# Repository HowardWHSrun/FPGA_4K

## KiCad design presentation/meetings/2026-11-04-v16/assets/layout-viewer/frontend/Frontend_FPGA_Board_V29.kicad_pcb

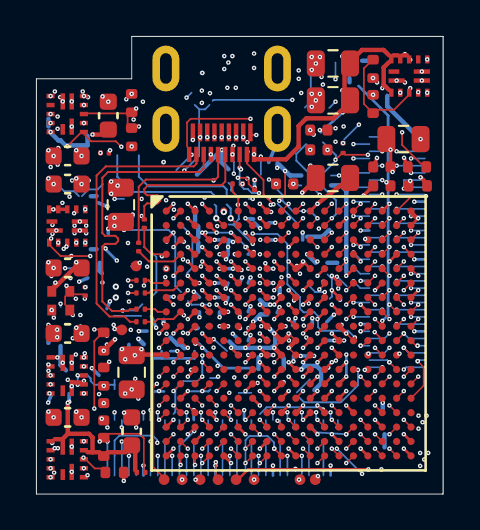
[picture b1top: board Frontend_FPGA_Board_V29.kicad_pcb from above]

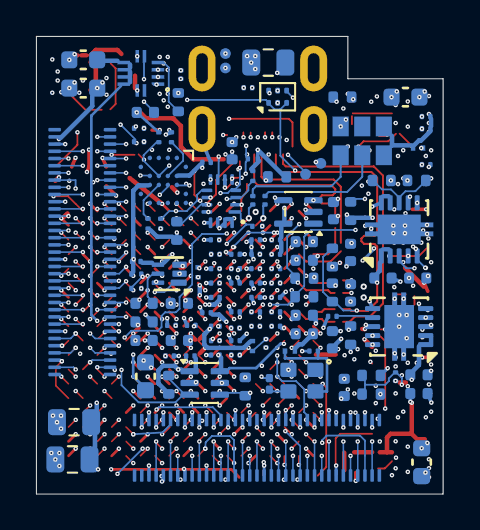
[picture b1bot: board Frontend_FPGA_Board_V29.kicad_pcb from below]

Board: 10 copper layers, 22.6 x 25.4 mm, 184 parts (124 on the bottom side), 191 nets.

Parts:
C1, C2, C12, C13, C21, C22, C85, C86: 22uF; C_0603_1608Metric
C3, C14, C23, C87: 22pF; C_0201_GRM03_Murata_0p22Gap
C4, C10, C89: 100uF; C_0805_2012Metric
C5, C6, C16, C17, C24, C25, C30, C31, C36, C37, C43, C44, C45, C47, C48, C49, C51, C54, C90, C94, C95, C96, C101: 4.7uF; C_0402_1005Metric
C7, C8, C9, C11, C18, C19, C20, C26, C27, C28, C29, C32, C33, C34, C35, C38, C39, C40, C52, C53, C55, C56, C57, C58, C80, C91, C92, C93, C97, C98, C99, C100: 470nF; C_0201_GRM03_Murata_0p22Gap
C15, C42, C59: 47uF; C_0805_2012Metric
C46, C50: 10nF; C_0201_GRM03_Murata_0p22Gap
C60, C63, C78, C79, C81, C82, C83, C88, C105, C106, C200, C201, C202, C203, C204, C205: 100nF; C_0201_GRM03_Murata_0p22Gap
C61, C84: 1uF; C_0402_1005Metric
C62: 220nF; C_0201_GRM03_Murata_0p22Gap
C75, C76, C102, C104: 22uF / 6.3V; C_0603_1608Metric
C77: 22nF / 50V; C_0402_1005Metric
C103: 470nF / 6.3V; C_0201_GRM03_Murata_0p22Gap
C206, C207, C208: 22uF / 10V; C_0805_2012Metric
J1, J2: DF40C-70DS-0.4V(51); Hirose_DF40C-70DS-0.4V_2x35_P0.4mm
J3: Micro-HDMI 467651001; Molex_MicroHDMI_46765_1xxx
L1, L2, L3, L4: MPZ0603S121HT000; TDK_MPZ0603S121HT000_0201_Land_0p25x0p30_Gap0p30
R1, R4, R5, R41, R55, R59: 200k; R_0402_1005Metric
R2: 301k; R_0402_1005Metric
R3, R9, R11, R12, R14, R17, R18, R19, R22, R38, R43, R58: 4.99k; R_0402_1005Metric
R7: 150k; R_0402_TE_CPF_Reflow_0p50Gap
R8: 100k; R_0402_TE_CPF_Reflow_0p50Gap
R10: 1.3k; R_0402_1005Metric
R13: 2.49k; R_0402_1005Metric
R16: 100R; R_0201_ERA1A_Panasonic_0p30Gap
R20, R21, R49, R50: 4.7k; R_0201_ERA1A_Panasonic_0p30Gap
R25: 470R; R_0402_1005Metric
R27: 1k; R_0201_ERA1A_Panasonic_0p30Gap
R37: 24k / 1%; R_0402_1005Metric
R42: 150k; R_0402_1005Metric
R44: 33R; R_0201_0603Metric
R45: 4.64k; R_0201_ERA1A_Panasonic_0p30Gap
R46, R47, R48: 10k; R_0201_ERA1A_Panasonic_0p30Gap
R51, R52, R53: 47k; R_0201_ERA1A_Panasonic_0p30Gap
R54: 22k; R_0201_ERA1A_Panasonic_0p30Gap
R57: 10k; R_0402_1005Metric
R60: 44.2k; R_0402_1005Metric
TP1, TP2, TP3, TP4, TP5, TP6, TP7, TP8, TP9, TP10, TP11, TP12, TP13, TP14: 0.6mm COPPER; TestPoint_Pad_D0.6mm_Edge_NoPaste
U1: XC7A35T-2CSG325I; Xilinx_CSG325
U2, U3, U4, U13, U16: MPM3834CGPA; MPM3834C_ECLGA14_2.5x2.5mm
U5, U6: TPS74801DRCRM3; VSON-10-1EP_3x3mm_P0.5mm_EP1.65x2.4mm
U7: W25Q128JWYIQ; Winbond_WLCSP-21_P0.5mm
U8: SN74AVC4T774RSVR / SPI x1; TI_RSV_UQFN16_1.8x2.6mm_P0.4mm
U10: MP5077GG-Z; MPS_MP5077_QFN12_2x2mm_P0.4mm
U11: 74AUP2G07GM / dual reset OD; Nexperia_SOT886_XSON6_1x1.45mm
U12: TPS389001 / timed rail-ready reset; TI_DSE0006A_WSON6_1p5x1p5_P0p5_Manufacturer
U14: SN74AUP1G14 / SPI OE; TI_DCK_SC70_5
U15: SN74AXC1T45DCKR; SOT-363_SC-70-6
Y1: AX3DAF1-125.0000T3 / 125 MHz; Abracon_AX3_3225_6pin
Y2: SiT1615A / 25 MHz / 1.5 V; SiTime_2016_4pin

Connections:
1V4_GTP_IN: C43.2, C47.2, C86.1, C87.1, R41.1, U5.1 (IN), U5.2 (IN), U6.1 (IN), U6.2 (IN), U13.6 (OUT_S), U13.9 (OUT), U13.10 (OUT)
/ASIC1_CLK32MHz_Out: J1.11, U1.P15 (L11P_T1_SRCC)
/ASIC1_DATA1: J1.3, U1.M16 (L7P_T1_D09)
/ASIC1_DATA2: J1.4, U1.N18 (L10P_T1_D14)
/ASIC1_DATA3: J1.5, U1.M17 (L7N_T1_D10)
/ASIC1_DATA4: J1.6, U1.P18 (L10N_T1_D15)
/ASIC1_DATA5: J1.7, U1.N16 (L9P_T1_DQS)
/ASIC1_DATA6: J1.8, U1.L18 (L4N_T0_D05)
/ASIC1_DATA7: J1.9, U1.K15 (L5N_T0_D07)
/ASIC1_DATA8: J1.10, U1.K18 (L3N_T0_DQS_EMCCLK)
/ASIC1_READ: J1.12, U1.K17 (L4P_T0_D04)
/ASIC1_SYNC: J1.13, U1.J15 (L2P_T0_D02)
/ASIC2_CLK32MHz_Out: J1.23, U1.E16 (L14P_T2_SRCC)
/ASIC2_DATA1: J1.18, U1.H18 (L23N_T3_FWE_B)
/ASIC2_DATA2: J1.21, U1.G14 (L22P_T3_A17)
/ASIC2_DATA3: J1.16, U1.H16 (L20P_T3_A20)
/ASIC2_DATA4: J1.17, U1.H14 (IO25)
/ASIC2_DATA5: J1.20, U1.H17 (L23P_T3_FOE_B)
/ASIC2_DATA6: J1.24, U1.G16 (L20N_T3_A19)
/ASIC2_DATA7: J1.22, U1.G17 (L19P_T3_A22)
/ASIC2_DATA8: J1.19, U1.G15 (L21P_T3_DQS)
/ASIC2_READ: J1.25, U1.F14 (L22N_T3_A16)
/ASIC2_SYNC: J1.26, U1.F18 (L19N_T3_A21_VREF)
/ASIC3_CLK32MHz_Out: J1.36, U1.E15 (L13P_T2_MRCC)
/ASIC3_DATA1: J1.31, U1.F15 (L21N_T3_DQS_A18)
/ASIC3_DATA2: J1.28, U1.F17 (L24P_T3_RS1)
/ASIC3_DATA3: J1.35, U1.D14 (L12N_T1_MRCC)
/ASIC3_DATA4: J1.30, U1.E18 (L24N_T3_RS0)
/ASIC3_DATA5: J1.29, U1.E13 (L12P_T1_MRCC)
/ASIC3_DATA6: J1.32, U1.E17 (L17P_T2_A26)
/ASIC3_DATA7: J1.39, U1.D15 (L13N_T2_MRCC)
/ASIC3_DATA8: J1.33, U1.D11 (L6P_T0)
/ASIC3_READ: J1.37, U1.C11 (L4P_T0)
/ASIC3_SYNC: J1.38, U1.D18 (L17N_T2_A25)
/ASIC4_CLK32MHz_Out: J1.43, U1.D13 (L11P_T1_SRCC)
/ASIC4_DATA1: J1.44, U1.C14 (L9P_T1_DQS_AD3P)
/ASIC4_DATA2: J1.40, U1.D16 (L14N_T2_SRCC)
/ASIC4_DATA3: J1.47, U1.C13 (L11N_T1_SRCC)
/ASIC4_DATA4: J1.45, U1.C9 (L2N_T0_AD8N)
/ASIC4_DATA5: J1.49, U1.C12 (L6N_T0_VREF)
/ASIC4_DATA6: J1.42, U1.C16 (L16P_T2_A28)
/ASIC4_DATA7: J1.53, U1.B12 (L7P_T1_AD2P)
/ASIC4_DATA8: J1.46, U1.B16 (L15P_T2_DQS)
/ASIC4_READ: J1.48, U1.B15 (L9N_T1_DQS_AD3N)
/ASIC4_SYNC: J1.51, U1.A13 (L8P_T1_AD10P)
/ASIC5_CLK32MHz_Out: J2.7, U1.R2 (L13P_T2_MRCC)
/ASIC5_DATA1: J2.11, U1.N2 (L11N_T1_SRCC)
/ASIC5_DATA2: J2.6, U1.U1 (L15N_T2_DQS)
/ASIC5_DATA3: J2.4, U1.P1 (L9N_T1_DQS)
/ASIC5_DATA4: J2.3, U1.N1 (L9P_T1_DQS)
/ASIC5_DATA5: J2.5, U1.K1 (L3N_T0_DQS)
/ASIC5_DATA6: J2.12, U1.U6 (L20P_T3)
/ASIC5_DATA7: J2.13, U1.L2 (L4N_T0)
/ASIC5_DATA8: J2.10, U1.U2 (L15P_T2_DQS)
/ASIC5_READ: J2.8, U1.T2 (L14N_T2_SRCC)
/ASIC5_SYNC: J2.9, U1.M1 (L7N_T1)
/ASIC6_CLK32MHz_Out: J2.20, U1.R3 (L14P_T2_SRCC)
/ASIC6_DATA1: J2.16, U1.R1 (L13N_T2_MRCC)
/ASIC6_DATA2: J2.19, U1.M2 (L7P_T1)
/ASIC6_DATA3: J2.24, U1.T4 (L17P_T2)
/ASIC6_DATA4: J2.17, U1.K2 (L3P_T0_DQS)
/ASIC6_DATA5: J2.18, U1.T3 (L17N_T2)
/ASIC6_DATA6: J2.25, U1.L3 (L5N_T0)
/ASIC6_DATA7: J2.22, U1.U4 (L18P_T2)
/ASIC6_DATA8: J2.23, U1.P3 (L12N_T1_MRCC)
/ASIC6_READ: J2.21, U1.K3 (L4P_T0)
/ASIC6_SYNC: J2.26, U1.V6 (L23N_T3)
/ASIC7_CLK32MHz_Out: J2.31, U1.P4 (L12P_T1_MRCC)
/ASIC7_DATA1: J2.33, U1.N4 (L10N_T1)
/ASIC7_DATA2: J2.30, U1.V4 (L18N_T2)
/ASIC7_DATA3: J2.29, U1.M4 (L10P_T1)
/ASIC7_DATA4: J2.36, U1.U7 (L23P_T3)
/ASIC7_DATA5: J2.28, U1.T5 (L21N_T3_DQS)
/ASIC7_DATA6: J2.32, U1.U5 (L20N_T3)
/ASIC7_DATA7: J2.35, U1.R5 (L21P_T3_DQS)
/ASIC7_DATA8: J2.37, U1.R6 (IO25)
/ASIC7_READ: J2.39, U1.R7 (L22P_T3)
/ASIC7_SYNC: J2.38, U1.V7 (L24N_T3)
/ASIC8_CLK32MHz_Out: J2.49, U1.R16 (L14P_T2_SRCC)
/ASIC8_DATA1: J2.53, U1.R17 (L14N_T2_SRCC)
/ASIC8_DATA2: J2.46, U1.V12 (L21P_T3_DQS)
/ASIC8_DATA3: J2.40, U1.U9 (L24P_T3_A01_D17)
/ASIC8_DATA4: J2.48, U1.U12 (L22N_T3_A04_D20)
/ASIC8_DATA5: J2.47, U1.T13 (L19N_T3_A09_D25_VREF)
/ASIC8_DATA6: J2.43, U1.U11 (L23P_T3_A03_D19)
/ASIC8_DATA7: J2.45, U1.T12 (L22P_T3_A05_D21)
/ASIC8_DATA8: J2.44, U1.V11 (L23N_T3_A02_D18)
/ASIC8_READ: J2.42, U1.V9 (L24N_T3_A00_D16)
/ASIC8_SYNC: J2.51, U1.T17 (L16P_T2_CSI_B)
/CLK25_RAW: R44.1, Y2.3 (OUT)
/CLK25_VDD: C88.1, L3.2, Y2.4 (VDD)
/FB_GTP_1V4: C87.2, R41.2, R42.1, U13.5 (FB)
/FB_VIN_3V3: R59.2, R60.1, U16.5 (FB)
/FE_RESET_SHARED: J1.64, U1.A15 (L10N_T1_AD11N)
/GPIO_CMD_N: J3.14 (GPIO_CMD_N), U1.V2 (L16N_T2)
/GPIO_CMD_P: J3.12 (GPIO_CMD_P), U1.V3 (L16P_T2)
/IMP_TST_SHARED: J1.63, U1.A12 (L7N_T1_AD2N)
/NONSTIM_BOARD1_SPI_DL: J1.58, U1.B17 (L16N_T2_A27)
/NONSTIM_BOARD1_SPI_DR: J1.59, U1.B11 (L4N_T0)
/NONSTIM_BOARD2_SPI_DL: J2.63, U1.U16 (L17N_T2_A13_D29)
/NONSTIM_BOARD2_SPI_DR: J2.59, U1.T14 (L13P_T2_MRCC)
/STIM_CHIP1_SPI_DL: J1.65, U1.A9 (L3N_T0_DQS_AD1N)
/STIM_CHIP1_SPI_DR: J1.60, U1.B14 (L10P_T1_AD11P)
/STIM_CHIP2_SPI_DL: J1.62, U1.A17 (L15N_T2_DQS_ADV_B)
/STIM_CHIP3_SPI_DL: J2.56, U1.V13 (L21N_T3_DQS_A06_D22)
/STIM_CHIP4_SPI_DR: J2.61, U1.T15 (L13N_T2_MRCC)
BOARD1_CLK: J1.56, U1.C17 (L18P_T2_A24)
BOARD1_SPI_CLK: J1.54, U1.C18 (L18N_T2_A23)
BOARD2_CLK: J1.61, U1.A10 (L5N_T0_AD9N)
BOARD2_SPI_CLK: J1.55, U1.B10 (L5P_T0_AD9P)
BOARD3_CLK: J2.54, U1.V8 (L24P_T3)
BOARD3_SPI_CLK: J2.55, U1.U10 (IO25)
BOARD4_CLK: J2.52, U1.T7 (L22N_T3)
BOARD4_SPI_CLK: J2.65, U1.T18 (L15N_T2_DQS_DOUT_CSO_B)
BOOT_RAILS_PG_3V3: R9.2, TP10.1 (PAD_1), U4.11 (PG), U5.3 (PG), U12.3 (MR_PG)
BOOT_RESET_N: R47.2, U11.1 (1A_RESET_N), U11.3 (2A_RESET_N), U12.6 (RESET_N_OD), U14.2 (A_RESET_N)
CABLE_TARGET_SENSE: J3.1 (SENSE), R27.2
CHIP_RESET_SHARED: J1.52, U1.J16 (L2N_T0_D03)
CLK25_PL: R44.2, U1.N3 (L11P_T1_SRCC)
EN_GTPWR_1V5: R58.2, U1.M15 (L6N_T0_D08_VREF), U15.3 (A)
EN_GTPWR_3V3: R57.1, U13.3 (EN), U15.4 (B)
FLASH_CS_N_1V8: R22.2, U7.1, U8.11 (B2_CS)
FLASH_DQ0_1V8: R53.2, U7.5, U8.10 (B3_MOSI)
FLASH_DQ1_1V8: R51.1, U7.2, U8.9 (B4_MISO)
FLASH_HOLD_N_1V8: R21.2, U7.7
FLASH_READY_SENSE: R45.2, R46.1, U12.1 (SENSE_DIV)
FLASH_SCK_1V8: R52.1, U7.6, U8.12 (B1_SCK)
FLASH_TRANSLATOR_OE_N: R48.2, U8.7 (OE_N), U14.4 (Y_OE_N)
FLASH_WP_N_1V8: R20.2, U7.3
FPGA_DONE: R38.2, TP12.1 (PAD_1), U1.F12 (DONE_0)
FPGA_INIT_B: R18.2, TP11.1 (PAD_1), U1.T10 (INIT_B_0), U11.4 (2Y_INIT_OD)
FPGA_JTAG_TCK: J3.17 (TCK), U1.F8 (TCK_0)
FPGA_JTAG_TDI: J3.15 (TDI), U1.T9 (TDI_0)
FPGA_JTAG_TDO: J3.18 (TDO), U1.T8 (TDO_0)
FPGA_JTAG_TMS: J3.2 (TMS), U1.R8 (TMS_0)
FPGA_PROGRAM_B: R17.2, U1.P10 (PROGRAM_B_0), U11.6 (1Y_PROGRAM_OD)
FPGA_PUDC_B: R25.2, U1.J18 (L3P_T0_DQS_PUDC_B)
FPGA_QSPI_CCLK: R49.2, U1.E8 (CCLK_0), U8.1 (A1_CCLK)
FPGA_QSPI_CS_N: R19.2, U1.L15 (L6P_T0_FCS_B), U8.2 (A2_CS)
FPGA_QSPI_DQ0: R50.2, U1.K16 (L1P_T0_D00_MOSI), U8.3 (A3_MOSI)
FPGA_QSPI_DQ1: R54.1, U1.L17 (L1N_T0_D01_DIN), U8.4 (A4_MISO)
GND: C1.2, C2.2, C4.2, C5.2, C6.2, C7.2, C8.2, C9.2, C10.2, C11.2, C12.2, C13.2, C15.2, C16.2, C17.2, C18.2, C19.2, C20.2, C21.2, C22.2, C24.2, C25.2, C26.2, C27.2, C28.2, C29.2, C30.2, C31.2, C32.2, C33.2, C34.2, C35.2, C36.2, C37.2, C38.2, C39.2, C40.2, C42.2, C43.1, C44.2, C45.2, C46.2, C47.1, C48.2, C49.2, C50.2, C51.2, C52.2, C53.2, C54.2, C55.2, C56.2, C58.2, C59.2, C60.2, C61.2, C62.2, C63.2, C75.2, C76.2, C77.2, C80.2, C81.2, C82.2, C83.2, C84.2, C85.2, C86.2, C88.2, C89.2, C90.2, C91.2, C92.2, C93.2, C94.2, C95.2, C96.2, C97.2, C98.2, C99.2, C100.2, C101.2, C102.2, C103.2, C104.2, C105.2, C106.2, C206.2, C207.2, C208.2, J1.14, J1.15, J1.27, J1.34, J1.41, J1.50, J1.66, J2.14, J2.15, J2.27, J2.34, J2.41, J2.50, J2.66, J3.4 (GND), J3.7 (GND), J3.10 (GND), J3.13 (GND), J3.16 (GND), J3.SH (SHIELD), L2.1, R2.2, R5.2, R8.2, R11.2, R14.2, R37.2, R42.2, R46.2, R51.2, R52.2, R54.2, R55.2, R57.2, R60.2, TP1.1 (PAD_1), TP13.1 (PAD_1), U1.A1 (GND_[75_balls]), U1.A3 (MGTPRXN1_216), U1.A4 (MGTPRXP1_216), U1.A5 (GND), U1.A7 (GND), U1.A8 (GND), U1.A11 (GND), U1.A18 (GND), U1.B3 (GND), U1.B7 (GND), U1.B8 (GND), U1.B18 (GND), U1.C2 (GND), U1.C3 (MGTPRXN2_216), U1.C4 (MGTPRXP2_216), U1.C6 (GND), U1.C7 (GND), U1.C15 (GND), U1.D3 (GND), U1.D4 (GND), U1.D7 (GND), U1.D12 (GND), U1.E2 (GND), U1.E3 (MGTPRXN0_216), U1.E4 (MGTPRXP0_216), U1.E6 (GND), U1.E7 (GND), U1.E9 (GND), U1.E12 (CFGBVS_0), U1.F4 (GND), U1.F6 (GND), U1.F10 (GND), U1.F13 (M2_0), U1.F16 (GND), U1.G1 (GND), U1.G3 (MGTPRXN3_216), U1.G4 (MGTPRXP3_216), U1.G5 (GND), U1.G6 (GND), U1.G7 (GND), U1.G9 (GND), U1.G11 (GND), U1.G13 (GND), U1.H3 (GND), U1.H4 (GND), U1.H5 (GND), U1.H6 (GND), U1.H8 (GND), U1.H10 (GND), U1.H12 (GND), U1.J1 (GND), U1.J2 (GND), U1.J3 (GND), U1.J7 (GND), U1.J11 (GND), U1.J13 (GND), U1.J17 (GND), U1.K4 (GND), U1.K8 (GND), U1.K12 (GND), U1.K14 (GND), U1.L1 (GND), U1.L7 (GND), U1.L11 (GND), U1.L13 (GND), U1.M8 (GND), U1.M9 (DXN_0), U1.M10 (DXP_0), U1.M12 (GND), U1.M18 (GND), U1.N5 (GND), U1.N7 (GND), U1.N9 (GND), U1.N11 (GND), U1.N13 (GND), U1.N15 (GND), U1.P2 (GND), U1.P8 (GND), U1.P12 (GND), U1.R9 (GND), U1.R11 (M1_0), U1.T6 (GND), U1.T16 (GND), U1.U3 (GND), U1.U13 (GND), U1.V1 (GND), U1.V10 (GND), U1.V18 (GND), U2.2 (PGND), U2.4 (AGND), U2.7 (PGND), U2.8 (PGND), U3.2 (PGND), U3.4 (AGND), U3.7 (PGND), U3.8 (PGND), U4.2 (PGND), U4.4 (AGND), U4.7 (PGND), U4.8 (PGND), U5.6 (GND), U5.11 (GND_EP), U6.6 (GND), U6.11 (GND_EP), U7.4, U8.6 (DIR4_L), U8.8 (GND), U10.2 (GND), U11.2 (GND), U12.2 (GND), U13.2 (PGND), U13.4 (AGND), U13.7 (PGND), U13.8 (PGND), U14.3 (GND), U15.2 (GND), U16.2 (PGND), U16.4 (AGND), U16.7 (PGND), U16.8 (PGND), Y1.3 (GND), Y2.2 (GND)
GNDADC_XADC: C57.2, L2.2, U1.J9 (GNDADC_0), U1.K9 (VREFN_0), U1.K10 (VP_0), U1.L9 (VN_0), U1.L10 (VREFP_0)
GTP_REFCLK1_N: C79.2, U1.B5 (MGTREFCLK1N_216)
GTP_REFCLK1_P: C78.2, U1.B6 (MGTREFCLK1P_216)
GTP_TX0_N: C201.1, J3.5 (TX0_REC_N)
GTP_TX0_P: C200.1, J3.3 (TX0_REC_P)
MGTAVCC_1V0: C45.1, C51.1, C52.1, C53.1, R10.1, TP7.1 (PAD_1), U1.B4 (MGTAVCC), U1.C5 (MGTAVCC), U1.E5 (MGTAVCC), U1.F5 (MGTAVCC), U5.9 (OUT), U5.10 (OUT)
MGTAVTT_1V2: C49.1, C54.1, C55.1, C56.1, R13.1, R16.1, TP8.1 (PAD_1), U1.A2 (MGTAVTT), U1.C1 (MGTAVTT), U1.E1 (MGTAVTT), U1.F3 (MGTAVTT), U1.G2 (MGTAVTT), U6.9 (OUT), U6.10 (OUT)
unnamed: C203.1, J3.8 (TX1_REC_N)
unnamed: C202.1, J3.6 (TX1_REC_P)
unnamed: C205.1, J3.11 (TX2_REC_N)
unnamed: C204.1, J3.9 (TX2_REC_P)
unnamed: C201.2, U1.H1 (MGTPTXN0_216)
unnamed: C203.2, U1.F1 (MGTPTXN1_216)
unnamed: C205.2, U1.D1 (MGTPTXN2_216)
unnamed: C200.2, U1.H2 (MGTPTXP0_216)
unnamed: C202.2, U1.F2 (MGTPTXP1_216)
unnamed: C204.2, U1.D2 (MGTPTXP2_216)
unnamed: R16.2, U1.A6 (MGTRREF_216)
unnamed: C3.2, R1.2, R2.1, U2.5 (FB)
unnamed: C14.2, R4.2, R5.1, R55.1, U3.5 (FB)
unnamed: C23.2, R7.2, R8.1, U4.5 (FB)
unnamed: R10.2, R11.1, U5.8 (FB)
unnamed: C46.1, U5.7 (SS)
unnamed: R13.2, R14.1, U6.8 (FB)
unnamed: C50.1, U6.7 (SS)
unnamed: R37.1, U10.4 (ILIM)
unnamed: C77.1, U10.5 (SS)
unnamed: C84.1, U12.5 (CT)
OSC125_3V3: C80.1, C81.1, L4.2, Y1.1 (OE), Y1.6 (VDD)
OSC125_N: C79.1, Y1.5 (OUTN)
OSC125_P: C78.1, Y1.4 (OUTP)
PG_CORE_1V0: R3.2, U2.11 (PG), U3.3 (EN), U4.3 (EN), U10.1 (EN)
PG_GTP_1V4: R43.2, U6.5 (EN), U13.11 (PG)
PG_MGT_1V2: R12.2, U5.5 (EN), U6.3 (PG)
SPI_LATCH_SHARED: J1.67, U1.A14 (L8N_T1_AD10N)
STIM_CHB_SHARED: J2.64, U1.U15 (L17P_T2_A14_D30)
STIM_CHIP2_SPI_DR: J1.57, U1.B9 (L3P_T0_DQS_AD1P)
STIM_CHIP3_SPI_DR: J2.57, U1.R13 (L19P_T3_A10_D26)
STIM_CHIP4_SPI_DL: J2.62, U1.V16 (L18P_T2_A12_D28)
STIM_CLK_SHARED: J2.67, U1.V17 (L18N_T2_A11_D27)
STIM_EN_SHARED: J2.58, U1.V14 (L20N_T3_A07_D23)
STIM_START_SHARED: J2.60, U1.U14 (L20P_T3_A08_D24)
SWITCHED_3V3: C76.1, C104.1, C106.1, L4.1, TP3.1 (PAD_1), U10.7 (VOUT), U10.8 (VOUT), U10.9 (VOUT), U10.10 (VOUT), U15.6 (VCCB)
VCCADC_1V8: C57.1, L1.2, U1.J10 (VCCADC_0)
VCCAUX_1V8: C13.1, C14.1, C15.1, C16.1, C17.1, C18.1, C19.1, C20.1, C58.1, C59.1, C60.1, C62.1, C94.1, C95.1, C96.1, C97.1, C98.1, C99.1, C100.1, L1.1, R4.1, R17.1, R18.1, R20.1, R21.1, R22.1, R27.1, R38.1, R45.1, R49.1, R53.1, TP5.1 (PAD_1), TP9.1 (PAD_1), U1.E10 (VCCO_0), U1.E11 (VCCBATT_0), U1.G12 (VCCAUX_[5_balls]), U1.H13 (VCCAUX), U1.K13 (VCCAUX), U1.M13 (VCCAUX), U1.P13 (VCCAUX), U1.R10 (VCCO_0), U1.R12 (M0_0), U3.6 (OUT_S), U3.9 (OUT), U3.10 (OUT), U7.8, U8.13 (VCCB_1V8)
VCCINT_1V0: C2.1, C3.1, C4.1, C5.1, C6.1, C7.1, C8.1, C9.1, C10.1, C11.1, C89.1, C90.1, C91.1, C92.1, C93.1, R1.1, TP4.1 (PAD_1), U1.F7 (VCCINT_1V0), U1.F9 (VCCINT_1V0), U1.F11 (VCCBRAM/VCCINT_[21_balls]), U1.G8 (VCCINT_1V0), U1.G10 (VCCBRAM_1V0), U1.H7 (VCCINT_1V0), U1.H9 (VCCINT_1V0), U1.H11 (VCCBRAM_1V0), U1.J8 (VCCINT_1V0), U1.J12 (VCCINT_1V0), U1.K7 (VCCINT_1V0), U1.K11 (VCCINT_1V0), U1.L8 (VCCINT_1V0), U1.L12 (VCCINT_1V0), U1.M7 (VCCINT_1V0), U1.M11 (VCCINT_1V0), U1.N8 (VCCINT_1V0), U1.N10 (VCCINT_1V0), U1.N12 (VCCINT_1V0), U1.P9 (VCCINT_1V0), U1.P11 (VCCINT_1V0), U2.6 (OUT_S), U2.9 (OUT), U2.10 (OUT)
VCCO_1V5: C22.1, C23.1, C24.1, C25.1, C26.1, C27.1, C28.1, C29.1, C30.1, C31.1, C32.1, C33.1, C34.1, C35.1, C36.1, C37.1, C38.1, C39.1, C40.1, C42.1, C61.1, C63.1, C101.1, C105.1, L3.1, R7.1, R19.1, R25.1, R48.1, R50.1, R58.1, TP6.1 (PAD_1), U1.A16 (VCCO), U1.B13 (VCCO), U1.C10 (VCCO), U1.D17 (VCCO), U1.E14 (VCCO), U1.G18 (VCCO), U1.H15 (VCCO), U1.L6 (VCCO), U1.L16 (VCCO), U1.M3 (VCCO), U1.P7 (VCCO), U1.P17 (VCCO), U1.R4 (VCCO), U1.R14 (VCCO), U1.T1 (VCCO), U1.T11 (VCCO), U1.U8 (VCCO), U1.U18 (VCCO), U1.V5 (VCCO), U1.V15 (VCCO), U4.6 (OUT_S), U4.9 (OUT), U4.10 (OUT), U8.5 (DIR3_H), U8.14 (VCCA_1V5), U8.15 (DIR1_H), U8.16 (DIR2_H), U14.5 (VCC_1V5), U15.1 (VCCA), U15.5 (DIR)
VIN_3V3: C1.1, C12.1, C21.1, C44.1, C48.1, C75.1, C82.1, C83.1, C85.1, C102.1, C103.1, C208.1, J1.68, R3.1, R9.1, R12.1, R43.1, R47.1, R59.1, TP2.1 (PAD_1), U2.3 (EN), U2.12 (IN), U2.13 (IN), U2.14 (IN), U3.12 (IN), U3.13 (IN), U3.14 (IN), U4.12 (IN), U4.13 (IN), U4.14 (IN), U5.4 (BIAS), U6.4 (BIAS), U10.3 (VCC), U10.6 (VIN), U10.11 (VIN), U11.5 (VCC_3V3), U12.4 (VDD_3V3), U13.12 (IN), U13.13 (IN), U13.14 (IN), U16.6 (OUT_S), U16.9 (OUT), U16.10 (OUT)
VIN_5V: C206.1, C207.1, J3.19 (5V_IN), TP14.1 (PAD_1), U16.3 (EN), U16.12 (IN), U16.13 (IN), U16.14 (IN)

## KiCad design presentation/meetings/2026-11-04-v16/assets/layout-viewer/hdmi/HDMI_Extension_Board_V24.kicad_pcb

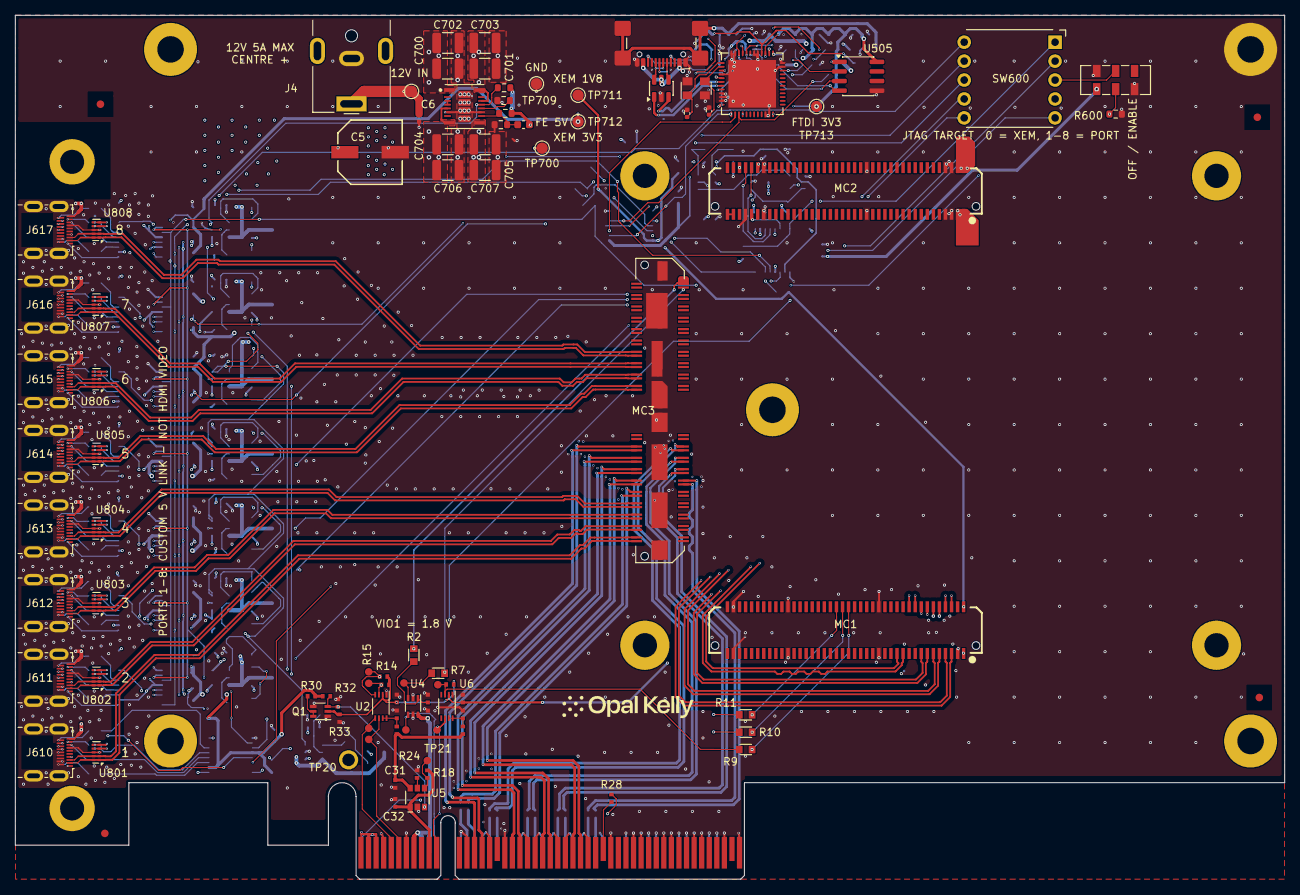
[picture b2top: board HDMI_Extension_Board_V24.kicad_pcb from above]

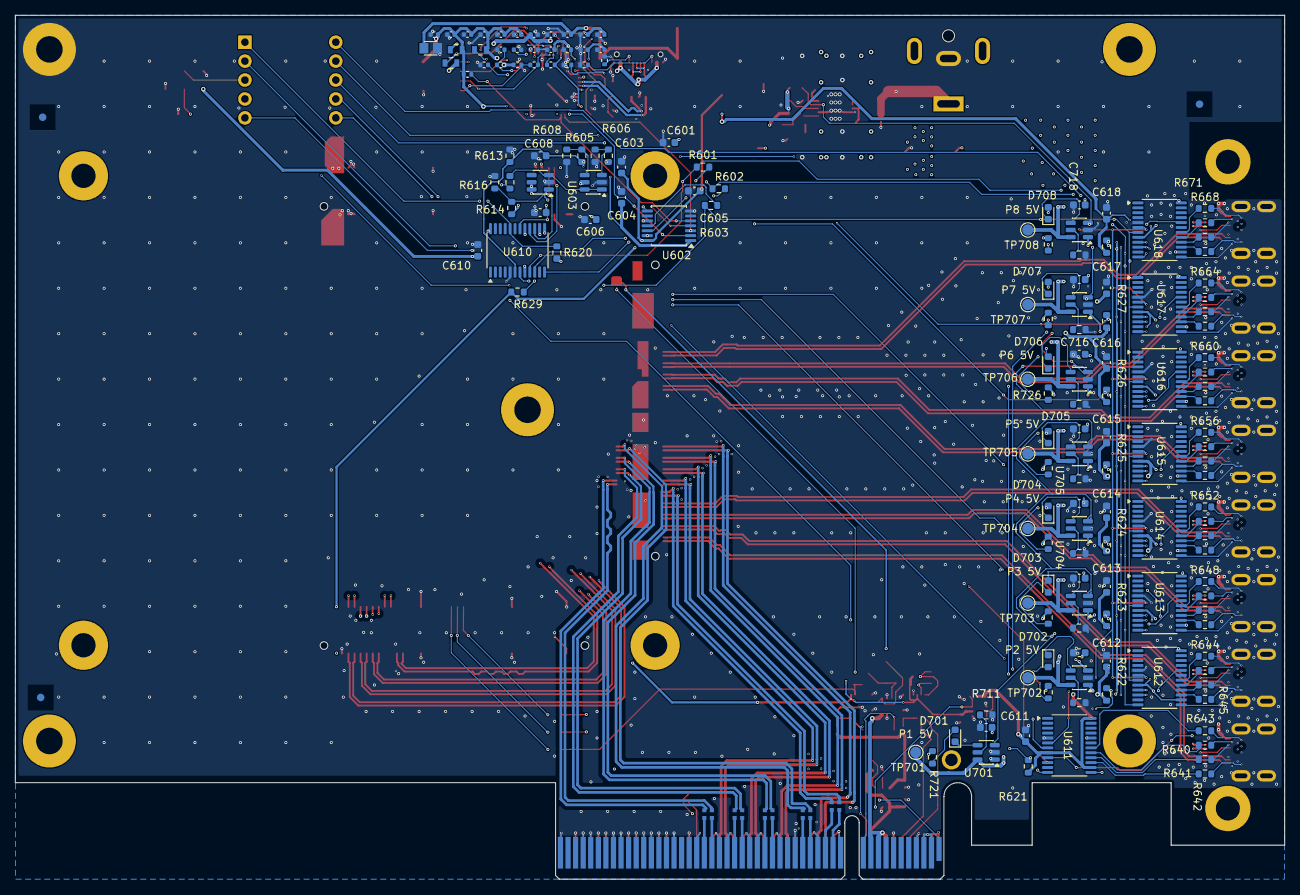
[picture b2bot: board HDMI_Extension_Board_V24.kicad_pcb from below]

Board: 6 copper layers, 167.6 x 114.1 mm, 275 parts (173 on the bottom side), 255 nets.

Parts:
*: Opal Kelly Logo; BRK_Logo_c689e08d
C5: EEE-FK1E221P; BRK_C5
C6: TMK105BJ104KV-F; BRK_C6
C7: C0402C104K8PACTU; BRK8310_C7
C8: C0402C104K8PACTU; BRK8310_C8
C9: C0402C104K8PACTU; BRK8310_C9
C10: C0402C104K8PACTU; BRK8310_C10
C11: C0402C104K8PACTU; BRK8310_C11
C12: C0402C104K8PACTU; BRK8310_C12
C13: C0402C104K8PACTU; BRK8310_C13
C14: C0402C104K8PACTU; BRK8310_C14
C15: C0402C104K8PACTU; BRK8310_C15
C16: C0402C104K8PACTU; BRK8310_C16
C17: C0402C104K8PACTU; BRK8310_C17
C18: C0402C104K8PACTU; BRK8310_C18
C19: C0402C104K8PACTU; BRK8310_C19
C20: C0402C104K8PACTU; BRK8310_C20
C27: C0402C104K8PACTU; BRK8310_C27
C28: C0402C104K8PACTU; BRK8310_C28
C31: C0402C104K8PACTU; BRK8310_C31
C32: C0402C104K8PACTU; BRK8310_C32
C500: 4.7u; C500
C501: 100n; C501
C502: 100n; C502
C503: 18p; C503
C504: 18p; C504
C505: 100n; C505
C506: 100n; C506
C507: 4.7u; C507
C508: 100n; C508
C509: 100n; C509
C510: 100n; C510
C511: 100n; C511
C512: 4.7u; C512
C513: 4.7u; C513
C514: 100n; C514
C515: 4.7u; C515
C516: 100n; C516
C517: 100n; C517
C518: 100n; C518
C519: 10n; C519
C601, C603: 2.2u; C_0603_1608Metric
C604, C605, C606, C609, C610, C611, C612, C613, C614, C615, C616, C617, C618: 100n; C_0603_1608Metric
C608: 1n; C_0603_1608Metric
C700, C701, C702, C703: 10uF; C_1210_3225Metric
C704, C705, C706, C707: 47uF; C_1210_3225Metric
C708: 22pF; C_0603_1608Metric
C711, C712, C713, C714, C715, C716, C717, C718: 100nF; C_0603_1608Metric
D500: USBLC6-2SC6; D500
D701, D702, D703, D704, D705, D706, D707, D708: RED; LED_0603_1608Metric
FB500: 600R; FB500
FB501: 600R; FB501
FB502: 600R; FB502
FB503: 220R @100MHz; FB503
FID1, FID5, FID6, FID7: FIDUCIAL; BRK_FID1
FID2: FIDUCIAL; BRK_FID2
FID3: FIDUCIAL; BRK_FID3
FID4: FIDUCIAL; BRK_FID4
J4: PJ-063AH; BarrelJack_CUI_PJ-063AH_Horizontal
J6: PCIe x8 Card-Edge Connector; BRK8310_J6
J500: USB4110-GF-A; J500
J610, J611, J612, J613, J614, J615, J616, J617: 467651001; HDMI_Micro-D_Molex_46765-1xxx
MC1: BTE-040-01-F-D-A; BRK_MC1
MC2: BTE-040-01-F-D-A; BRK_MC2
MC3: QTH-040-01-F-D-DP-A; BRK_MC3
MH1: MTG; BRK_MH1
MH2: MTG; BRK_MH2
MH3: MTG; BRK_MH3
MH4: MTG; BRK_MH4
Q1: SI1922EDH-T1-GE3; BRK8310_Q1
R2: CRCW06030000Z0EA; BRK8310_R2
R7: CRCW06030000Z0EA; BRK8310_R7
R9: CRCW06030000Z0EA; BRK8310_R9
R10: CRCW06030000Z0EA; BRK8310_R10
R11: CRCW06030000Z0EA; BRK8310_R11
R13: CRCW0402200KFKED; BRK8310_R13
R14: CRCW04024K75FKED; BRK8310_R14
R15: CRCW04024K75FKED; BRK8310_R15
R18: CRCW0402100KFKED; BRK8310_R18
R23: CRCW0402200KFKED; BRK8310_R23
R24: CRCW0402100KFKED; BRK8310_R24
R25: CRCW0402100KFKED; BRK8310_R25
R28: CRCW04020000Z0ED; BRK8310_R28
R30: CRCW04024K75FKED; BRK8310_R30
R31: CRCW04024K75FKED; BRK8310_R31
R32: CRCW0402100KFKED; BRK8310_R32
R33: CRCW0402100KFKED; BRK8310_R33
R500: 5.1k 1%; R500
R501: 5.1k 1%; R501
R502: 100k; R502
R503: 100k; R503
R504: 2k; R504
R505: 10k; R505
R506: 10k; R506
R507: 12k 1%; R507
R509: 10k; R509
R600, R721, R722, R723, R724, R725, R726, R727, R728: 3.3k; R_0603_1608Metric
R601, R602, R603: 22R; R_0603_1608Metric
R605: 301k; R_0603_1608Metric
R606, R608, R616: 100k; R_0603_1608Metric
R607: 402k; R_0603_1608Metric
R613: 68k; R_0603_1608Metric
R614: 4.7k; R_0603_1608Metric
R615: 12k; R_0603_1608Metric
R620, R621, R622, R623, R624, R625, R626, R627, R628, R701, R703: 10k; R_0603_1608Metric
R629: 1k; R_0603_1608Metric
R640, R641, R642, R643, R644, R645, R646, R647, R648, R649, R650, R651, R652, R653, R654, R655, R656, R657, R658, R659, R660, R661, R662, R663, R664, R665, R666, R667, R668, R669, R670, R671: 100R; R_0603_1608Metric
R700: 40.2k; R_0603_1608Metric
R702: 13k; R_0603_1608Metric
R711, R712, R713, R714, R715, R716, R717, R718: 37.4k; R_0603_1608Metric
SW600: SRBQ490100; ALPS_SRBQ490100_1P9T
SW601: JS202011JCQN; SW700
TP9: SMDAT_VIO; BRK8310_TP9
TP10: SMDAT_PCIE; BRK8310_TP10
TP11: SMCLK_PCIE; BRK8310_TP11
TP12: SMCLK_VIO; BRK8310_TP12
TP13: PERST_VIO; BRK8310_TP13
TP14: PERST_PCIE; BRK8310_TP14
TP15: WAKE_VIO; BRK8310_TP15
TP16: WAKE_PCIE; BRK8310_TP16
TP20: +12V_PCIE_C; BRK8310_TP20
TP21: FAULT; BRK8310_TP21
TP700, TP701, TP702, TP703, TP704, TP705, TP706, TP707, TP708, TP709: TestPoint; TestPoint_Pad_D1.5mm
TP710: 12V_IN; TestPoint_Pad_D1.5mm
TP711: 1V8_XEM; TestPoint_Pad_D1.5mm
TP712: 3V3_XEM; TestPoint_Pad_D1.5mm
TP713: 3V3_FTDI; TestPoint_Pad_D1.5mm
U2: PCA9306DCUR; BRK8310_U2
U4: SN74AXC1T45DCK; BRK8310_U4
U5: AP22653AW6-7; BRK8310_U5
U6: PCA9306DCUR; BRK8310_U6
U501: FT232HQ-REEL; U501
U505: 93LC56BT-I/SN; SOIC-8_3.9x4.9mm_P1.27mm
U602: TXU0304PWR; TSSOP-14_4.4x5mm_P0.65mm
U603: TPS3700DDCR; SOT-23-6
U605: TPS3808G30DBVR; SOT-23-6
U610, U611, U612, U613, U614, U615, U616, U617, U618: TS3A27518EPWR; TSSOP-24_4.4x7.8mm_P0.65mm
U700: TPSM63606RDLR; TI_TPSM63606_RDL0020A_EVM
U701, U702, U703, U704, U705, U706, U707, U708: TPS2553DBVR; SOT-23-6
U801, U802, U803, U804, U805, U806, U807, U808: TPD4E02B04DQAR; USON-10_2.5x1.0mm_P0.5mm
Y500: 7U12000E18UCG 12MHz; Y500

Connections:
+1.2V_DDR: MC3.80, R2.2
+1.8V: C603.1, C605.1, MC1.2, R629.2, TP711.1, U602.14
+3.3V: C601.1, C606.1, C609.1, C610.1, C611.1, C612.1, C613.1, C614.1, C615.1, C616.1, C617.1, C618.1, MC2.70, R30.2, R31.2, R615.1, R620.1, R621.1, R622.1, R623.1, R624.1, R625.1, R626.1, R627.1, R628.1, SW601.5, TP712.1, U603.5, U605.5, U605.6, U610.8, U610.14, U610.24, U611.8, U611.14, U611.24, U612.8, U612.14, U612.24, U613.8, U613.14, U613.24, U614.8, U614.14, U614.24, U615.8, U615.14, U615.24, U616.8, U616.14, U616.24, U617.8, U617.14, U617.24, U618.8, U618.14, U618.24
+3.3VAUX_PCIE: C31.2, R13.2, R23.2, U5.6
+3.3VAUX_PCIE_C: C32.2, J6.B10, R18.2, U5.1
+3.3V_PCIE_C: C12.2, J6.A9, J6.A10, J6.B8, U4.6
+VDCIN: C5.1, C6.2, C700.1, C701.1, C702.1, C703.1, J4.1, MC2.1, MC2.2, MC2.3, MC2.4, TP710.1, U700.1, U700.14, U700.16
/+12V_PCIE_C: J6.A2, J6.A3, J6.B1, J6.B2, J6.B3, TP20.1
/FTDI3V3_PHY: C515.1, C516.1, FB501.2, U501.3
/FTDI3V3_PLL: C513.1, C514.1, FB500.2, U501.8
/FTDI5V_FILTERED: C500.1, C501.1, FB502.2, U501.40
/FTDI_EECLK: R503.2, U501.44, U505.2
/FTDI_EECS: R502.1, U501.45, U505.1
/FTDI_EEDATA: R504.1, U501.43, U505.3
/PCIE_PERST_B_3V3: J6.A11, TP14.1, U4.4
/PCIE_PERST_B_VIO: R7.1, TP13.1, U4.3
/PCIE_PRSNT1_B: J6.A1, R28.2
/PCIE_REFCLKN_C: C8.1, J6.A14
/PCIE_REFCLKP_C: C7.1, J6.A13
/PCIE_RX0N_C: C14.1, J6.A17
/PCIE_RX0P_C: C13.1, J6.A16
/PCIE_RX1N_C: C16.1, J6.A22
/PCIE_RX1P_C: C15.1, J6.A21
/PCIE_RX2N_C: C18.1, J6.A26
/PCIE_RX2P_C: C17.1, J6.A25
/PCIE_RX3N_C: C20.1, J6.A30
/PCIE_RX3P_C: C19.1, J6.A29
/PCIE_SMCLK_3V3: J6.B5, TP11.1, U2.5
/PCIE_SMCLK_VIO: R11.1, R14.1, TP12.1, U2.4
/PCIE_SMDAT_3V3: J6.B6, TP10.1, U2.6
/PCIE_SMDAT_VIO: R10.1, R15.1, TP9.1, U2.3
/PCIE_WAKE_B_3V3: J6.B11, TP16.1, U6.6
/PCIE_WAKE_B_VIO: R9.1, R25.1, TP15.1, U6.3
/VIO_PG: Q1.3, R31.1, R32.2, U5.3
B64_L1N: J610.14, MC1.12, U801.5, U801.6
B64_L1P: J610.12, MC1.10, U801.4, U801.7
B64_L2N: J611.14, MC1.16, U802.5, U802.6
B64_L2P: J611.12, MC1.14, U802.4, U802.7
B64_L3N: J612.14, MC1.15, U803.5, U803.6
B64_L3P: J612.12, MC1.13, U803.4, U803.7
B64_L4N: J613.14, MC1.8, U804.5, U804.6
B64_L4P: J613.12, MC1.6, U804.4, U804.7
B64_L5N: J614.14, MC1.7, U805.5, U805.6
B64_L5P: J614.12, MC1.5, U805.4, U805.7
B64_L6N: J615.14, MC1.11, U806.5, U806.6
B64_L6P: J615.12, MC1.9, U806.4, U806.7
B64_L7N: J616.14, MC1.23, U807.5, U807.6
B64_L7P: J616.12, MC1.21, U807.4, U807.7
B64_L8N: J617.14, MC1.20, U808.5, U808.6
B64_L8P: J617.12, MC1.18, U808.4, U808.7
B64_L17N: MC1.44, R11.2
B64_L17P: MC1.42, R10.2
B64_L20N: MC1.40, R9.2
B67_T3U_N12: MC3.78, R7.2
DGND: C5.2, C6.1, C9.1, C10.1, C11.1, C12.1, C27.1, C28.1, C31.1, C32.1, C500.2, C501.2, C502.2, C503.2, C504.2, C505.2, C506.1, C507.2, C508.2, C509.2, C510.2, C511.2, C512.2, C513.2, C514.2, C515.2, C516.2, C517.1, C518.1, C519.2, C601.2, C603.2, C604.2, C605.2, C606.2, C608.2, C609.2, C610.2, C611.2, C612.2, C613.2, C614.2, C615.2, C616.2, C617.2, C618.2, C700.2, C701.2, C702.2, C703.2, C704.2, C705.2, C706.2, C707.2, C711.2, C712.2, C713.2, C714.2, C715.2, C716.2, C717.2, C718.2, D500.2, FB503.1, J4.2, J6.A4, J6.A12, J6.A15, J6.A18, J6.A20, J6.A23, J6.A24, J6.A27, J6.A28, J6.A31, J6.A34, J6.A37, J6.A38, J6.A41, J6.A42, J6.A45, J6.A46, J6.A49, J6.B4, J6.B7, J6.B13, J6.B16, J6.B18, J6.B21, J6.B22, J6.B25, J6.B26, J6.B29, J6.B32, J6.B35, J6.B36, J6.B39, J6.B40, J6.B43, J6.B44, J6.B47, J6.B49, J500.A1, J500.A12, J500.B1, J500.B12, J610.4, J610.7, J610.10, J610.13, J610.16, J610.SH, J611.4, J611.7, J611.10, J611.13, J611.16, J611.SH, J612.4, J612.7, J612.10, J612.13, J612.16, J612.SH, J613.4, J613.7, J613.10, J613.13, J613.16, J613.SH, J614.4, J614.7, J614.10, J614.13, J614.16, J614.SH, J615.4, J615.7, J615.10, J615.13, J615.16, J615.SH, J616.4, J616.7, J616.10, J616.13, J616.16, J616.SH, J617.4, J617.7, J617.10, J617.13, J617.16, J617.SH, MC1.3, MC1.29, MC1.30, MC1.59, MC1.60, MC1.77, MC1.78, MC2.5, MC2.6, MC2.7, MC2.8, MC2.33, MC2.34, MC2.67, MC2.68, MC2.73, MC3.0, Q1.1, Q1.4, R24.1, R32.1, R33.1, R500.1, R501.2, R502.2, R507.2, R600.2, R606.1, R608.1, R613.2, R616.2, R701.1, R702.1, R711.1, R712.1, R713.1, R714.1, R715.1, R716.1, R717.1, R718.1, SW601.1, SW601.7, TP709.1, U2.1, U4.2, U4.5, U5.2, U6.1, U501.4, U501.9, U501.10, U501.11, U501.22, U501.23, U501.35, U501.36, U501.41, U501.42, U501.47, U501.48, U501.PAD, U505.5, U602.7, U603.2, U605.2, U610.5, U611.5, U612.5, U613.5, U614.5, U615.5, U616.5, U617.5, U618.5, U700.6, U700.11, U700.17, U700.18, U700.19, U700.20, U701.2, U702.2, U703.2, U704.2, U705.2, U706.2, U707.2, U708.2, U801.3, U801.8, U802.3, U802.8, U803.3, U803.8, U804.3, U804.8, U805.3, U805.8, U806.3, U806.8, U807.3, U807.8, U808.3, U808.8, Y500.2, Y500.4
DRIVE_ENABLE: R615.2, R616.1, U602.8, U605.1
FE_5V: C704.1, C705.1, C706.1, C707.1, C708.1, C711.1, C712.1, C713.1, C714.1, C715.1, C716.1, C717.1, C718.1, R700.2, R703.2, R721.2, R722.2, R723.2, R724.2, R725.2, R726.2, R727.2, R728.2, TP700.1, U700.5, U700.8, U700.9, U701.1, U702.1, U703.1, U704.1, U705.1, U706.1, U707.1, U708.1
FTDI3V3: C505.1, C507.1, C508.1, C509.1, C510.1, C511.1, C512.1, C604.1, FB500.1, FB501.1, R503.1, R505.2, R506.1, R509.2, TP713.1, U501.12, U501.24, U501.39, U501.46, U505.8, U602.1
GNDADC: MC2.77, MC2.79
HDMI1_JTAG_TCK: J610.17, R640.2
HDMI1_JTAG_TDI: J610.15, R641.2
HDMI1_JTAG_TDO: J610.18, R643.2
HDMI1_JTAG_TMS: J610.2, R642.2
HDMI1_VREF: J610.1, U611.13
HDMI2_JTAG_TCK: J611.17, R644.2
HDMI2_JTAG_TDI: J611.15, R645.2
HDMI2_JTAG_TDO: J611.18, R647.2
HDMI2_JTAG_TMS: J611.2, R646.2
HDMI2_VREF: J611.1, U612.13
HDMI3_JTAG_TCK: J612.17, R648.2
HDMI3_JTAG_TDI: J612.15, R649.2
HDMI3_JTAG_TDO: J612.18, R651.2
HDMI3_JTAG_TMS: J612.2, R650.2
HDMI3_VREF: J612.1, U613.13
HDMI4_JTAG_TCK: J613.17, R652.2
HDMI4_JTAG_TDI: J613.15, R653.2
HDMI4_JTAG_TDO: J613.18, R655.2
HDMI4_JTAG_TMS: J613.2, R654.2
HDMI4_VREF: J613.1, U614.13
HDMI5_JTAG_TCK: J614.17, R656.2
HDMI5_JTAG_TDI: J614.15, R657.2
HDMI5_JTAG_TDO: J614.18, R659.2
HDMI5_JTAG_TMS: J614.2, R658.2
HDMI5_VREF: J614.1, U615.13
HDMI6_JTAG_TCK: J615.17, R660.2
HDMI6_JTAG_TDI: J615.15, R661.2
HDMI6_JTAG_TDO: J615.18, R663.2
HDMI6_JTAG_TMS: J615.2, R662.2
HDMI6_VREF: J615.1, U616.13
HDMI7_JTAG_TCK: J616.17, R664.2
HDMI7_JTAG_TDI: J616.15, R665.2
HDMI7_JTAG_TDO: J616.18, R667.2
HDMI7_JTAG_TMS: J616.2, R666.2
HDMI7_VREF: J616.1, U617.13
HDMI8_JTAG_TCK: J617.17, R668.2
HDMI8_JTAG_TDI: J617.15, R669.2
HDMI8_JTAG_TDO: J617.18, R671.2
HDMI8_JTAG_TMS: J617.2, R670.2
HDMI8_VREF: J617.1, U618.13
HOST_TCK: U501.13, U602.2
HOST_TDI: U501.14, U602.3
HOST_TDO: R509.1, U501.15, U602.5
HOST_TMS: U501.16, U602.4
JTAG_TCK: MC2.76, U610.17
JTAG_TCK_1V8: R601.2, U610.9, U611.9, U612.9, U613.9, U614.9, U615.9, U616.9, U617.9, U618.9
JTAG_TDI: MC2.74, U610.16
JTAG_TDI_1V8: R602.2, U610.12, U611.12, U612.12, U613.12, U614.12, U615.12, U616.12, U617.12, U618.12
JTAG_TDO: MC2.71, U610.18
JTAG_TDO_1V8: U602.10, U610.10, U611.10, U612.10, U613.10, U614.10, U615.10, U616.10, U617.10, U618.10
JTAG_TMS: MC2.72, U610.15
JTAG_TMS_1V8: R603.2, U610.7, U611.7, U612.7, U613.7, U614.7, U615.7, U616.7, U617.7, U618.7
MASTER: R600.1, R614.1, SW601.6
MGT_REFCLK1N_225_C: C8.2, MC3.19
MGT_REFCLK1P_225_C: C7.2, MC3.17
MGT_RXN0_224: J610.5, MC3.3, U801.2, U801.9
MGT_RXN0_225: J6.B28, MC3.23
MGT_RXN0_226: J614.5, MC3.43, U805.2, U805.9
MGT_RXN1_224: J611.5, MC3.7, U802.2, U802.9
MGT_RXN1_225: J6.B24, MC3.27
MGT_RXN1_226: J615.5, MC3.47, U806.2, U806.9
MGT_RXN2_224: J612.5, MC3.11, U803.2, U803.9
MGT_RXN2_225: J6.B20, MC3.31
MGT_RXN2_226: J616.5, MC3.51, U807.2, U807.9
MGT_RXN3_224: J613.5, MC3.15, U804.2, U804.9
MGT_RXN3_225: J6.B15, MC3.35
MGT_RXN3_226: J617.5, MC3.55, U808.2, U808.9
MGT_RXP0_224: J610.3, MC3.1, U801.1, U801.10
MGT_RXP0_225: J6.B27, MC3.21
MGT_RXP0_226: J614.3, MC3.41, U805.1, U805.10
MGT_RXP1_224: J611.3, MC3.5, U802.1, U802.10
MGT_RXP1_225: J6.B23, MC3.25
MGT_RXP1_226: J615.3, MC3.45, U806.1, U806.10
MGT_RXP2_224: J612.3, MC3.9, U803.1, U803.10
MGT_RXP2_225: J6.B19, MC3.29
MGT_RXP2_226: J616.3, MC3.49, U807.1, U807.10
MGT_RXP3_224: J613.3, MC3.13, U804.1, U804.10
MGT_RXP3_225: J6.B14, MC3.33
MGT_RXP3_226: J617.3, MC3.53, U808.1, U808.10
MGT_TXN0_225: C20.2, MC3.24
MGT_TXN1_225: C18.2, MC3.28
MGT_TXN2_225: C16.2, MC3.32
MGT_TXN3_225: C14.2, MC3.36
MGT_TXP0_225: C19.2, MC3.22
MGT_TXP1_225: C17.2, MC3.26
MGT_TXP2_225: C15.2, MC3.30
MGT_TXP3_225: C13.2, MC3.34
unnamed: C502.1, FB503.2, J500.M1, J500.M2, J500.M3, J500.M4
unnamed: D701.2, R721.1
unnamed: D701.1, U701.4
unnamed: D702.2, R722.1
unnamed: D702.1, U702.4
unnamed: D703.2, R723.1
unnamed: D703.1, U703.4
unnamed: D704.2, R724.1
unnamed: D704.1, U704.4
unnamed: D705.2, R725.1
unnamed: D705.1, U705.4
unnamed: D706.2, R726.1
unnamed: D706.1, U706.4
unnamed: D707.2, R727.1
unnamed: D707.1, U707.4
unnamed: D708.2, R728.1
unnamed: D708.1, U708.4
unnamed: J6.B31, R28.1
unnamed: J500.A5, R500.2
unnamed: J500.B5, R501.1
unnamed: Q1.5, Q1.6, R30.1
unnamed: R18.1, TP21.1, U5.4
unnamed: C10.2, R13.1, U2.7, U2.8
unnamed: C11.2, R2.1, U4.1
unnamed: R24.2, U5.5
unnamed: C28.2, R23.1, U6.7, U6.8
unnamed: C503.1, U501.1, Y500.1
unnamed: C504.1, U501.2, Y500.3
unnamed: R507.1, U501.5
unnamed: C518.2, U501.37
unnamed: C517.2, U501.38
unnamed: C519.1, R506.2, U501.34
unnamed: R504.2, R505.1, U505.4
unnamed: R601.1, U602.13
unnamed: R602.1, U602.12
unnamed: R603.1, U602.11
unnamed: R605.2, R606.2, U603.3
unnamed: R607.2, R608.2, U603.4
unnamed: R629.1, U610.13
unnamed: R642.1, U611.15
unnamed: R640.1, U611.17
unnamed: R643.1, U611.18
unnamed: R641.1, U611.16
unnamed: R646.1, U612.15
unnamed: R644.1, U612.17
unnamed: R647.1, U612.18
unnamed: R645.1, U612.16
unnamed: R650.1, U613.15
unnamed: R648.1, U613.17
unnamed: R651.1, U613.18
unnamed: R649.1, U613.16
unnamed: R654.1, U614.15
unnamed: R652.1, U614.17
unnamed: R655.1, U614.18
unnamed: R653.1, U614.16
unnamed: R658.1, U615.15
unnamed: R656.1, U615.17
unnamed: R659.1, U615.18
unnamed: R657.1, U615.16
unnamed: R662.1, U616.15
unnamed: R660.1, U616.17
unnamed: R663.1, U616.18
unnamed: R661.1, U616.16
unnamed: R666.1, U617.15
unnamed: R664.1, U617.17
unnamed: R667.1, U617.18
unnamed: R665.1, U617.16
unnamed: R670.1, U618.15
unnamed: R668.1, U618.17
unnamed: R671.1, U618.18
unnamed: R669.1, U618.16
unnamed: U700.3, U700.4
unnamed: C708.2, R700.1, R701.2, U700.10
unnamed: R702.2, U700.12
unnamed: R711.2, U701.5
unnamed: R712.2, U702.5
unnamed: R713.2, U703.5
unnamed: R714.2, U704.5
unnamed: R715.2, U705.5
unnamed: R716.2, U706.5
unnamed: R717.2, U707.5
unnamed: R718.2, U708.5
PORT1_5V: J610.19, TP701.1, U701.6
PORT2_5V: J611.19, TP702.1, U702.6
PORT3_5V: J612.19, TP703.1, U703.6
PORT4_5V: J613.19, TP704.1, U704.6
PORT5_5V: J614.19, TP705.1, U705.6
PORT6_5V: J615.19, TP706.1, U706.6
PORT7_5V: J616.19, TP707.1, U707.6
PORT8_5V: J617.19, TP708.1, U708.6
PORT_ENABLE: R703.1, U700.13, U701.3, U702.3, U703.3, U704.3, U705.3, U706.3, U707.3, U708.3
ROTARY_COMMON: SW600.3, SW601.2
SEL_0: R620.2, SW600.1, U610.20
SEL_1: R621.2, SW600.2, U611.20
SEL_2: R622.2, SW600.4, U612.20
SEL_3: R623.2, SW600.5, U613.20
SEL_4: R624.2, SW600.6, U614.20
SEL_5: R625.2, SW600.7, U615.20
SEL_6: R626.2, SW600.8, U616.20
SEL_7: R627.2, SW600.9, U617.20
SEL_8: R628.2, SW600.10, U618.20
USB5V: C506.2, D500.5, FB502.1, J500.A4, J500.A9, J500.B4, J500.B9
USB_DM_CONN: D500.4, J500.A7, J500.B7
USB_DP_CONN: D500.6, J500.A6, J500.B6
USB_D_N: D500.3, U501.6
USB_D_P: D500.1, U501.7
VIO1: C9.2, C27.2, MC1.1, Q1.2, R14.2, R15.2, R25.2, R33.2, U2.2, U6.2
VREF_SELECTED: C608.1, R605.1, R607.1, R613.1, U610.6, U611.6, U612.6, U613.6, U614.6, U615.6, U616.6, U617.6, U618.6
WINDOW_GATE: R614.2, U603.1, U603.6, U605.3
